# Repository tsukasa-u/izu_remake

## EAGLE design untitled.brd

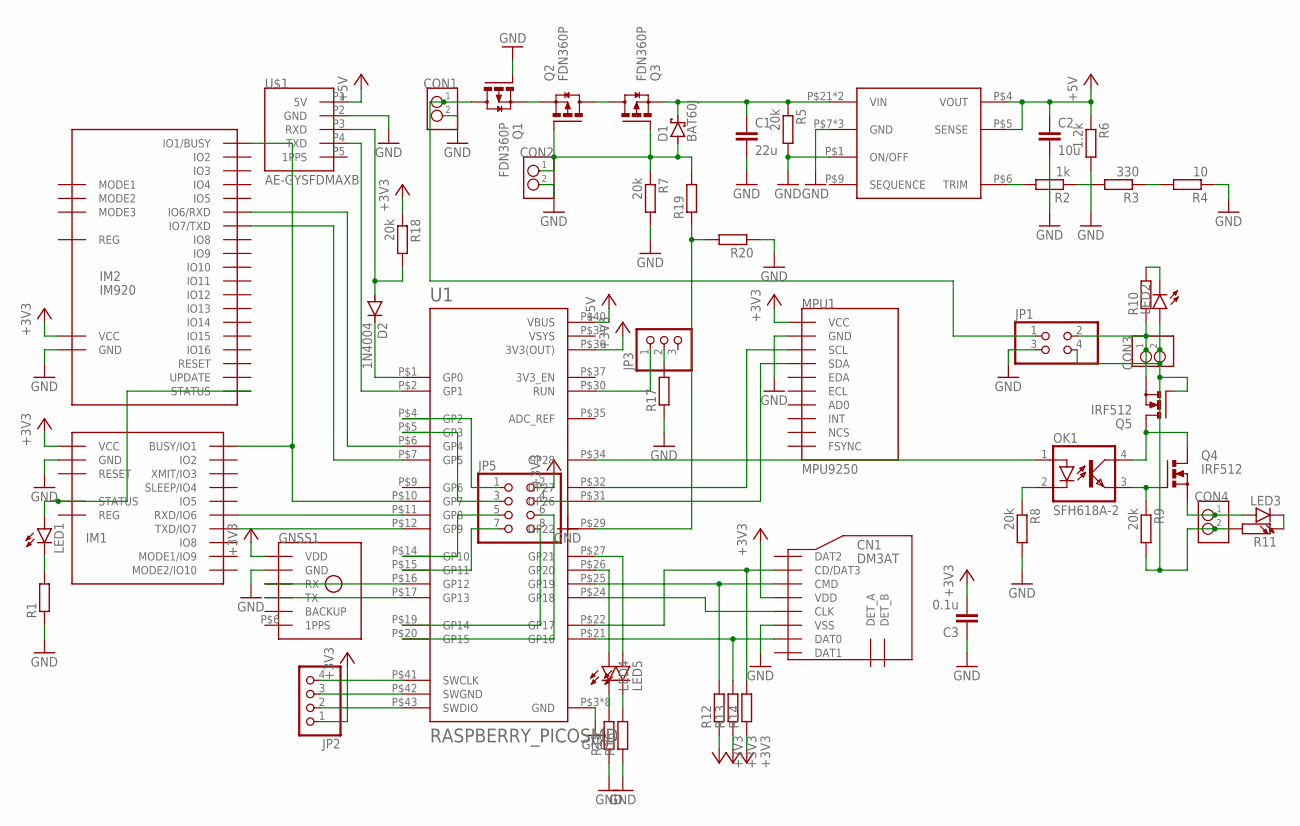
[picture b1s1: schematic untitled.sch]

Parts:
C1: 22u; C0805
C2: 10u; C0805
C3: 0.1u; C0805
CN1: DM3AT
CON1, CON2, CON3, CON4: B2B-XH-A
D1: BAT60J; SOD323_ST
D2: 1N4004; DO41-10
GNSS1: GYSFDMAXB
I1: ＯＫＬ-Ｔ/３-Ｗ５Ｎ-Ｃ
IM1: IM920C
IM2: IM920
JP1: PINHD-2X2; 2X02
JP2: PINHD-1X4; 1X04
JP3: PINHD-1X3; 1X03
JP5: PINHD-2X4; 2X04
LED1, LED2, LED3, LED4, LED5: LEDCHIP-LED0805; CHIP-LED0805
MPU1: MPU9250; GY-9250
OK1: SFH618A-2; DIP4
Q1, Q2, Q3: FDN360P; SUPER-SOT3
Q4, Q5: IRF512; TO220BV
R1, R10, R11, R12, R13, R14, R15, R16, R17, R19, R20: R-EU_R0603; R0603
R2: 1k; R0603
R3: 330; R0603
R4: 10; R0603
R5, R7, R8, R9, R18: 20k; R0603
R6: 1.2k; R0603
U1: RASPBERRY_PICOSMD; PICO-PKG-SMD
U$1: AE-GYSFDMAXB

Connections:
+3V3: C3.2, CN1.VDD, GNSS1.P$16 (VDD), IM1.$P17 (VCC), IM2.IO23 (VCC), JP2.1, JP5.2, MPU1.P1 (VCC), R12.1, R13.1, R14.1, R18.1, U1.P$36 (3V3(OUT))
+5V: C2.1, I1.P$4 (VOUT), I1.P$5 (SENSE), R6.1, U1.P$40 (VBUS), U$1.P1 (5V)
GND: C1.2, C2.2, C3.1, CN1.VSS, CON1.P$2 (2), CON2.P$2 (2), GNSS1.P$1 (GND), GNSS1.P$2 (GND), GNSS1.P$7 (GND), GNSS1.P$10 (GND), GNSS1.P$12 (GND), GNSS1.P$19 (GND), GNSS1.P$20 (GND), I1.P$1 (ON/OFF), I1.P$7 (GND), I1.P$31 (GND), I1.P$32 (GND), IM1.$P18 (GND), IM2.IO24 (GND), JP1.3, JP5.4, MPU1.P2 (GND), Q1.1 (G), R1.1, R4.1, R5.2, R6.2, R7.2, R8.2, R15.1, R16.1, R17.1, R20.1, U1.P$3 (GND), U1.P$8 (GND), U1.P$13 (GND), U1.P$18 (GND), U1.P$23 (GND), U1.P$28 (GND), U1.P$33 (GND), U1.P$38 (GND), U$1.P2 (GND)
unnamed: CN1.CLK, U1.P$24 (GP18)
unnamed: CN1.DAT0, R13.2, U1.P$21 (GP16)
unnamed: CN1.CMD, R12.2, U1.P$25 (GP19)
unnamed: CN1.CD/DAT3, R14.2, U1.P$22 (GP17)
unnamed: MPU1.P4 (SDA), U1.P$31 (GP26)
unnamed: MPU1.P3 (SCL), U1.P$32 (GP27)
unnamed: GNSS1.P$3 (RX), U1.P$16 (GP12)
unnamed: GNSS1.P$5 (TX), U1.P$17 (GP13)
unnamed: IM1.$P6 (RXD/IO6), U1.P$11 (GP8)
unnamed: IM1.$P7 (TXD/IO7), U1.P$12 (GP9)
unnamed: LED1.C, R1.2
unnamed: IM1.$P15 (STATUS), IM2.IO21 (STATUS), LED1.A
unnamed: IM1.$P1 (BUSY/IO1), IM2.IO1 (IO1/BUSY), U1.P$10 (GP7)
unnamed: IM2.IO6 (IO6/RXD), U1.P$6 (GP4)
unnamed: IM2.IO7 (IO7/TXD), U1.P$7 (GP5)
unnamed: U1.P$2 (GP1), U$1.P4 (TXD)
unnamed: D2.C, U1.P$1 (GP0)
unnamed: R2.1, R3.2
unnamed: I1.P$6 (TRIM), R2.2
unnamed: R3.1, R4.2
unnamed: CON1.P$1 (1), JP1.1, Q1.3 (D)
unnamed: C1.1, D1.C, I1.P$21 (VIN), I1.P$22 (VIN), Q3.2 (S), R5.1
unnamed: Q1.2 (S), Q2.2 (S)
unnamed: Q2.3 (D), Q3.3 (D)
unnamed: R19.1, R20.2, U1.P$29 (GP22)
unnamed: OK1.2 (C), R8.1
unnamed: OK1.3 (EMIT), Q4.G, R9.1
unnamed: CON4.P$1 (1), LED3.A, Q4.S
unnamed: CON3.P$1 (1), JP1.2, Q5.S, R10.1
unnamed: OK1.4 (COL), Q4.D, Q5.D
unnamed: OK1.1 (A), U1.P$34 (GP28)
unnamed: CON3.P$2 (2), CON4.P$2 (2), JP1.4, LED2.A, Q5.G, R9.2, R11.2
unnamed: LED3.C, R11.1
unnamed: LED2.C, R10.2
unnamed: JP2.2, U1.P$43 (SWDIO)
unnamed: JP2.3, U1.P$42 (SWGND)
unnamed: JP2.4, U1.P$41 (SWCLK)
unnamed: JP5.6, U1.P$20 (GP15)
unnamed: JP5.8, U1.P$19 (GP14)
unnamed: JP5.7, U1.P$15 (GP11)
unnamed: JP5.5, U1.P$14 (GP10)
unnamed: JP5.3, U1.P$5 (GP3)
unnamed: JP5.1, U1.P$4 (GP2)
unnamed: LED4.A, U1.P$26 (GP20)
unnamed: LED5.A, U1.P$27 (GP21)
unnamed: LED4.C, R15.2
unnamed: LED5.C, R16.2
unnamed: JP3.1, U1.P$30 (RUN)
unnamed: JP3.2, R17.2
unnamed: D2.A, R18.2, U$1.P3 (RXD)
unnamed: CON2.P$1 (1), D1.A, Q2.1 (G), Q3.1 (G), R7.1, R19.2
VSYS: U1.P$39 (VSYS)

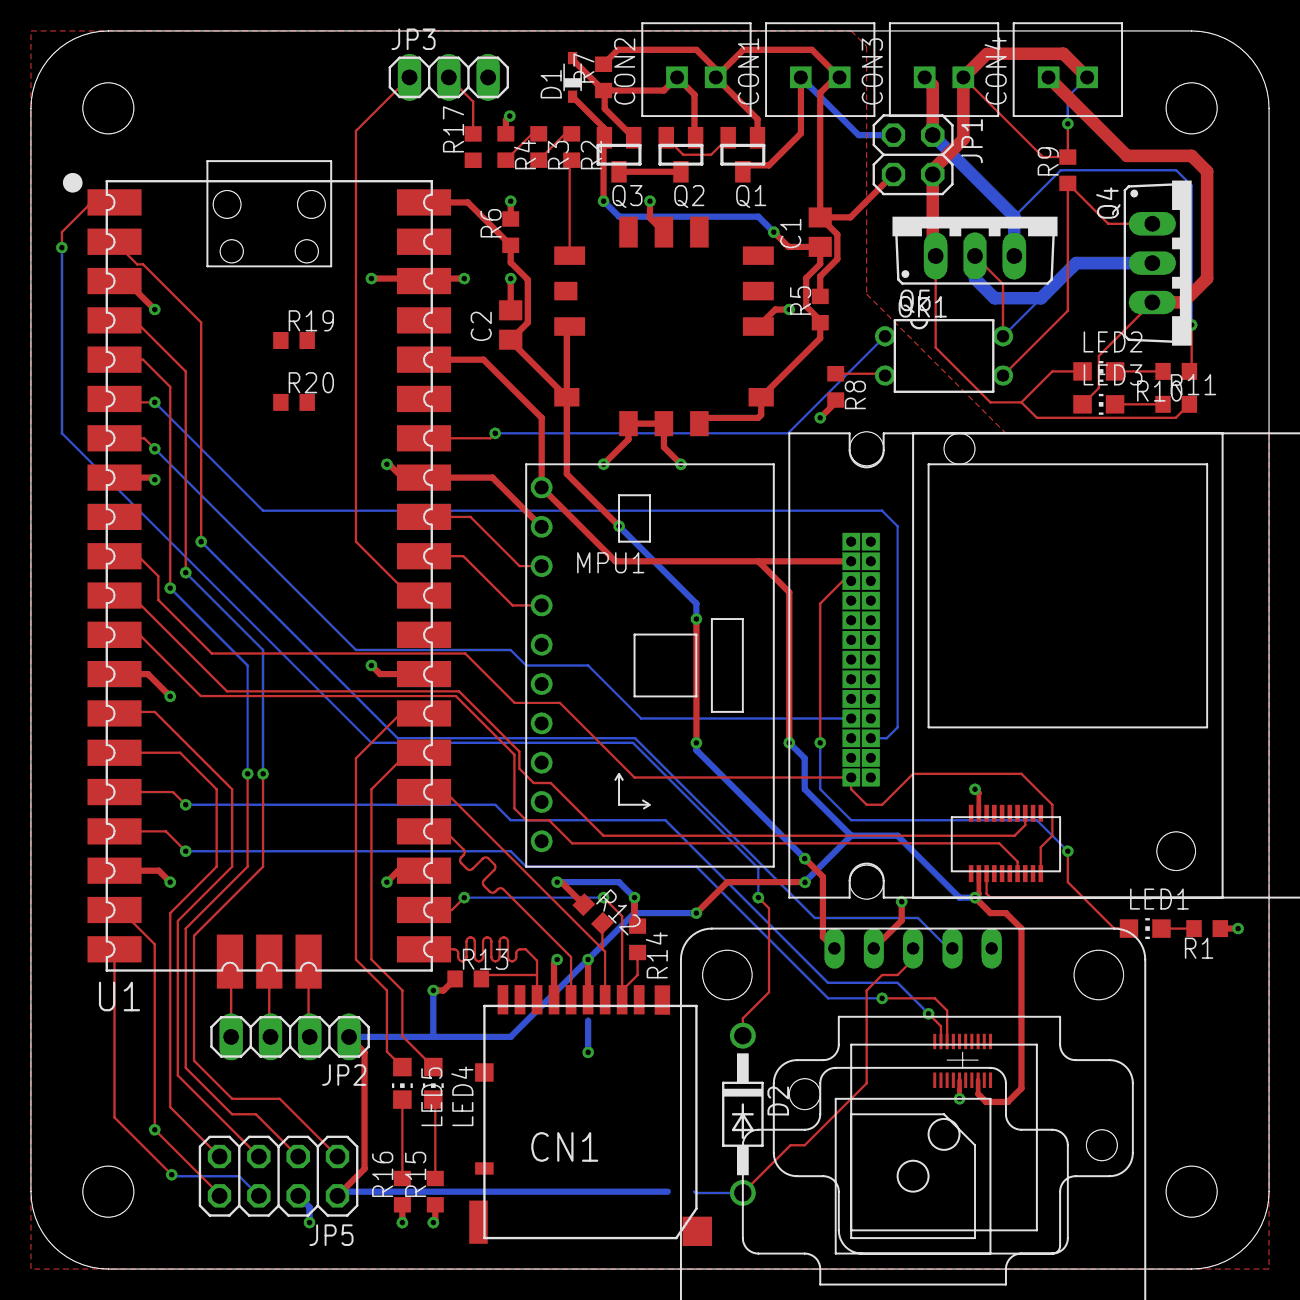
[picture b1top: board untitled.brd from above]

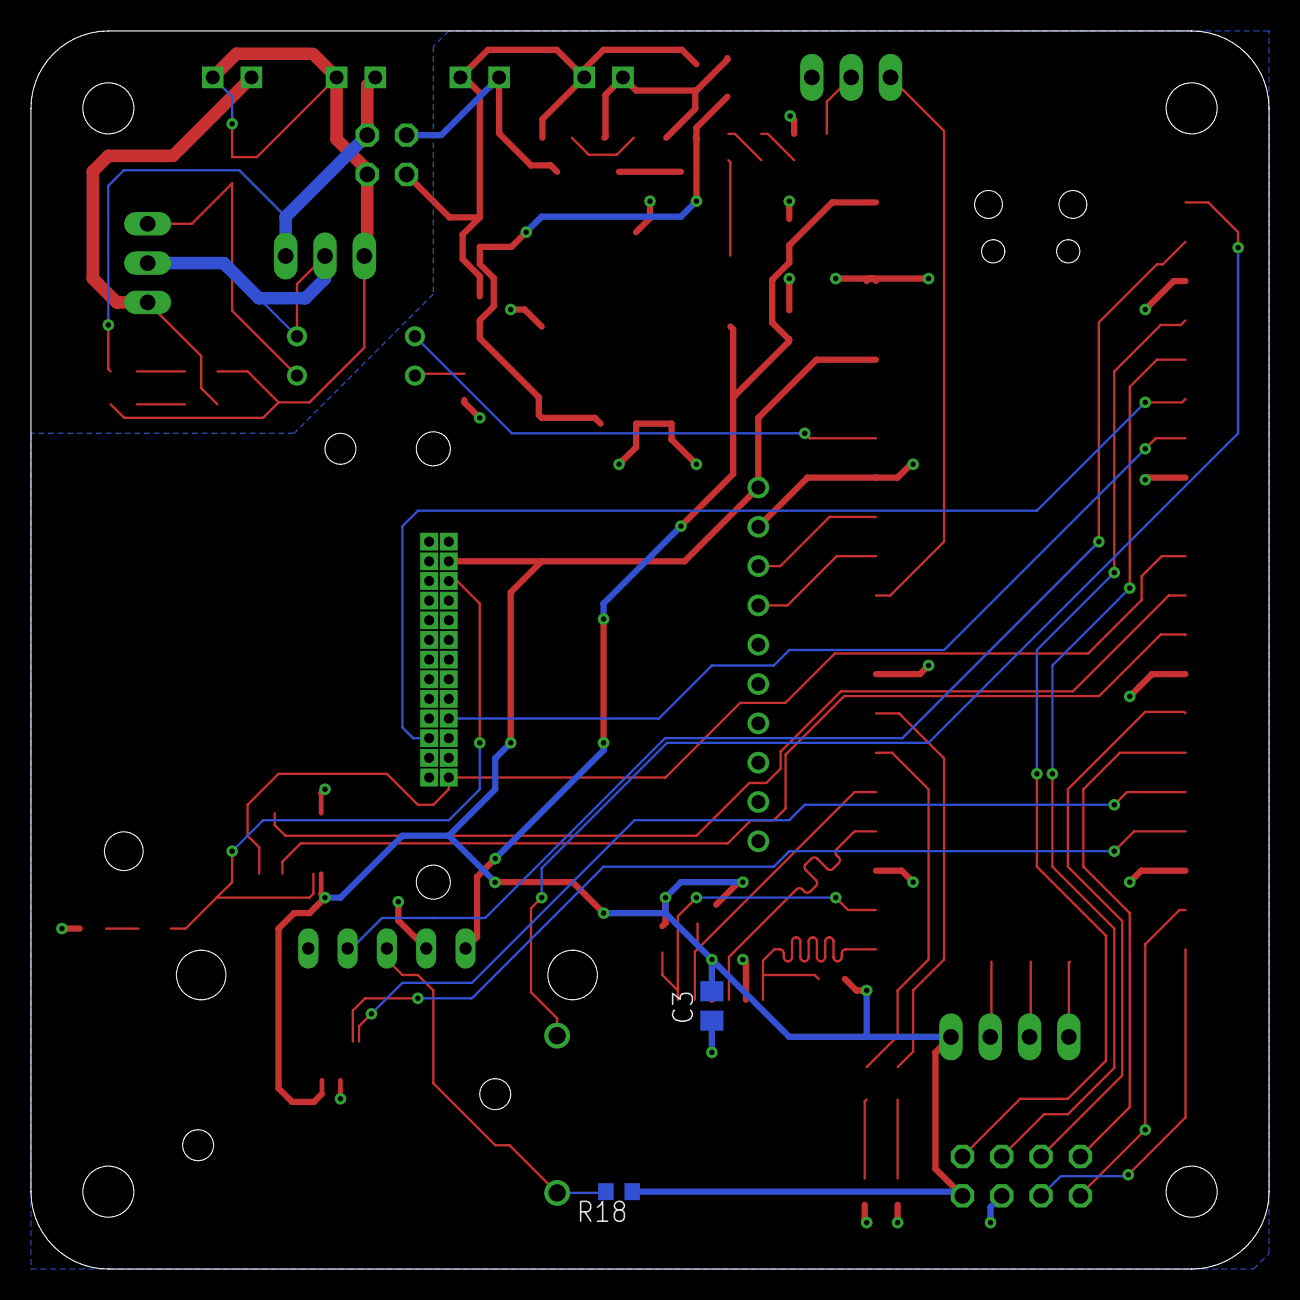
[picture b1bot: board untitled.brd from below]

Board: 2 copper layers, 80.0 x 80.0 mm, 52 parts (2 on the bottom side), 54 nets.

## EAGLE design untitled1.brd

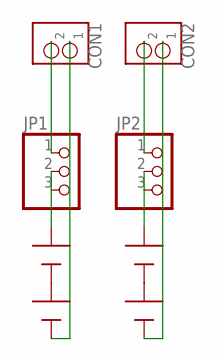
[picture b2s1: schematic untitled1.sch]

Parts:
CON1, CON2: B2B-XH-A
JP1, JP2: PINHD-1X3; 1X03
U$1, U$2, U$3, U$4: CR123A

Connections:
unnamed: CON1.P$2 (2), JP1.1
unnamed: CON1.P$1 (1), U$3.-
unnamed: CON2.P$2 (2), JP2.1
unnamed: CON2.P$1 (1), U$4.-
unnamed: U$2.-, U$4.+
unnamed: JP1.2, JP1.3, U$1.+
unnamed: U$1.-, U$3.+
unnamed: JP2.2, JP2.3, U$2.+

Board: 2 copper layers, 8 parts (0 on the bottom side), 8 nets, no tracks yet.
